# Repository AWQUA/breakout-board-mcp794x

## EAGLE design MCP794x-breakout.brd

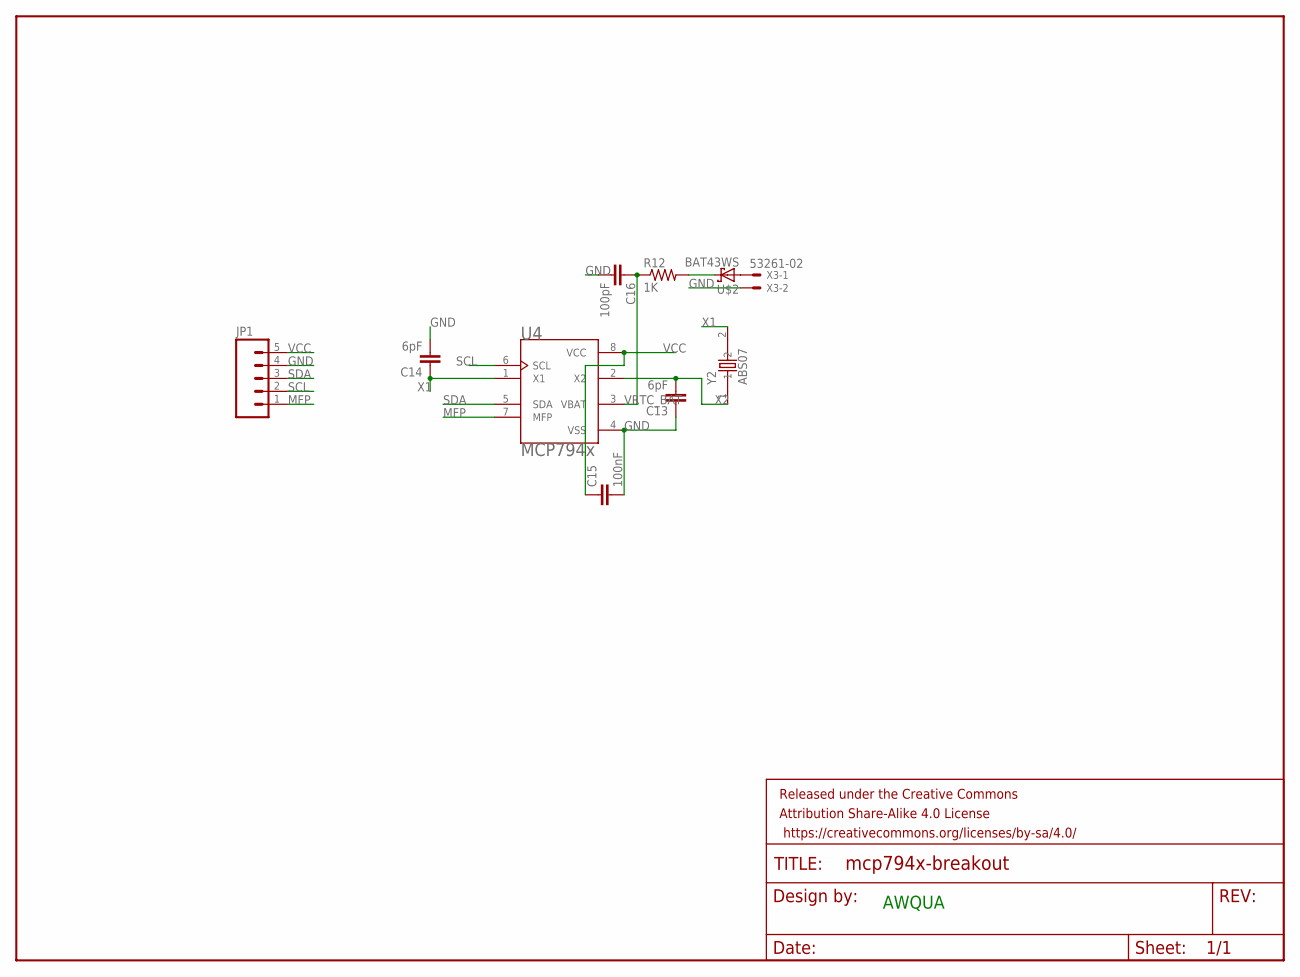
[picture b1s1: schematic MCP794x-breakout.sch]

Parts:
C13, C14: 6pF; 0603-CAP
C15: 100nF; 0603-CAP
C16: 100pF; 0603-CAP
FRAME1: FRAME-LETTER; CREATIVE_COMMONS
JP1: M05PTH; 1X05
R12: 1K; 0603-RES
U4: MCP794x; SOIC127P600X175-8N
U$2: BAT43WS
X3: 53261-02
Y2: ABS07; XTAL320X150X90

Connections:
GND: C13.1, C14.2, C15.2, C16.2, JP1.4, U4.4 (VSS), X3.2
MFP: JP1.1, U4.7 (MFP)
unnamed: U$2.PIN1 (C), X3.1
unnamed: R12.2, U$2.PIN2 (A)
SCL: JP1.2, U4.6 (SCL)
SDA: JP1.3, U4.5 (SDA)
VCC: C15.1, JP1.5, U4.8 (VCC)
VRTC_BAT: C16.1, R12.1, U4.3 (VBAT)
X1: C14.1, U4.1 (X1), Y2.2
X2: C13.2, U4.2 (X2), Y2.1

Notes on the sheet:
AWQUA

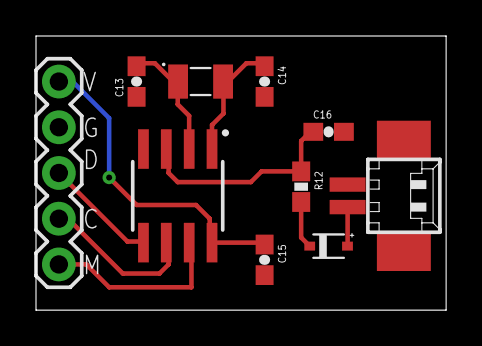
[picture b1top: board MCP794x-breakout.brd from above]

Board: 2 copper layers, 22.8 x 15.2 mm, 11 parts (0 on the bottom side), 10 nets.

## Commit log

2017-09-13 initial board push
2017-09-14 labels fixed

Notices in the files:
parts and their libraries:
SparkFun-Passives: Licensing: Creative Commons ShareAlike 4.0 International - https://creativecommons.org/licenses/by-sa/4.0
SparkFun-Aesthetics: Released under the Creative Commons
Attribution Share-Alike 4.0 License
SparkFun-Aesthetics: (https://creativecommons.org/licenses/by-sa/4.0/)
